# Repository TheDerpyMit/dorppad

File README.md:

# dorppad
heya! this is DorpPad, (or NikoKaltryxPad). It is a 6 button macropad with a rotate encoder meant for games or productivity!

# Features!!
- 6 customizable buttons for max productivity!
- a *beautiful* rotary encoder for volume control or whatever you wish :D
- pretty bulky (i will probably redesign this baha) case with 2 led's

i also wanted to leave a hole for the led's to shine through but i decided i can probably cut out the case and put thin blured out plastic to make it look like pixels but i wasn't so sure about it so i didn't do it in this version..

the code is very incomplete and mostly chatgpt since i plan on redoing it when i get the parts to make this 🥹

# Assembly

# PCB

# Schmatic

# Case parts!!

Back case to hold the PCB

Front cover so it looks beautiful!

And finally the whole case put together! (insert drumroll sound!!)

# BOM
| Item | Quantity | Price (USD) |
|-----|----------|-------------|
| Cherry MX Low Profile Switches | 6x | 1.26 |
| Blank DSA Keycaps | 6x | 1.50 |
| Xiao RP2040 | 1x | 6.75 |
| EC11B5AI Rotary Encoder | 1x | 0.61 |
| PCB | 1x | 9.82 |
| **Total (Approx.)** |  | **18-20 USD** |

# thank you so much for viewing this btw this was a very fun project to do! 💖

update: i will probably update this design so its more visually appealing since there's a lot of things i wanna fix

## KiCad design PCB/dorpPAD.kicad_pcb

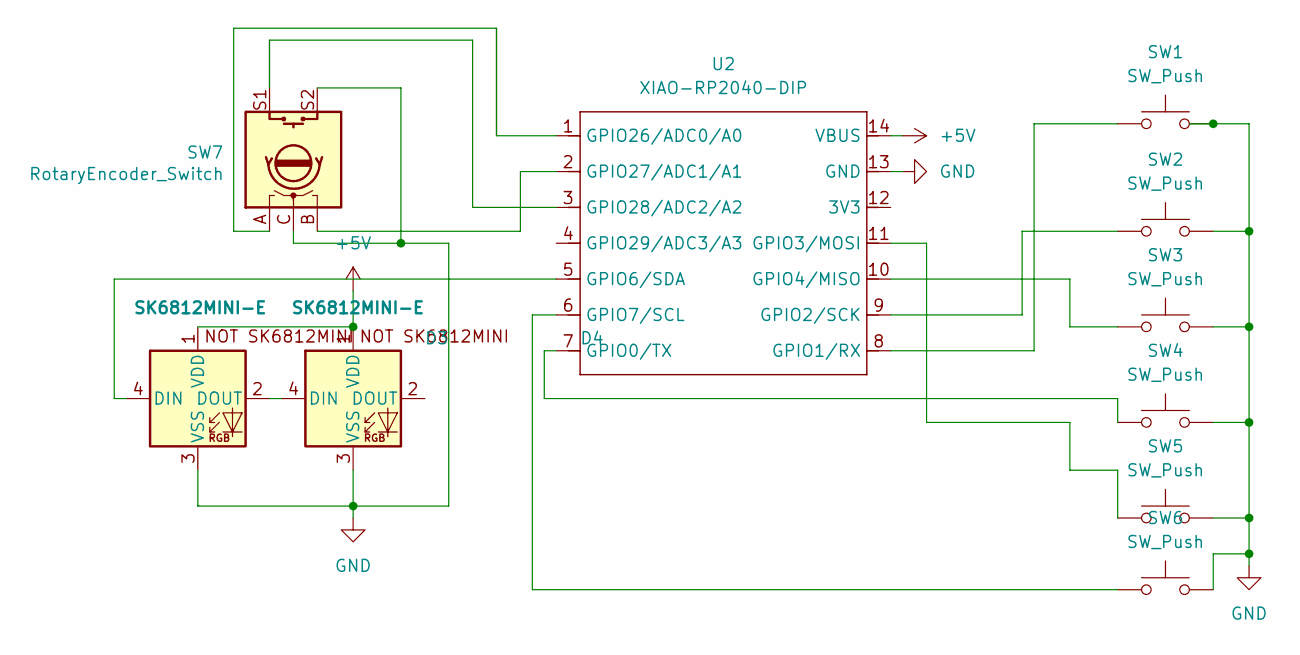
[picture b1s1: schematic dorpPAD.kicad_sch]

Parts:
D3, D4: SK6812MINI-E; MX_SK6812MINI-E_REV
SW1, SW2, SW3, SW4, SW5, SW6: SW_Push; SW_Cherry_MX_1.00u_PCB
SW7: RotaryEncoder_Switch; RotaryEncoder_Alps_EC11E-Switch_Vertical_H20mm
U2: XIAO-RP2040-DIP

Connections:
+5V: D3.1 (VDD), D4.1 (VDD), U2.14 (VBUS)
GND: D3.3 (VSS), D4.3 (VSS), SW1.2, SW2.2, SW3.2, SW4.2, SW5.2, SW6.2, SW7.C, SW7.S2, U2.13 (GND)
unnamed: D3.4 (DIN), U2.5 (GPIO6/SDA)
unnamed: D3.2 (DOUT), D4.4 (DIN)
unnamed: SW4.1, U2.7 (GPIO0/TX)
unnamed: SW1.1, U2.8 (GPIO1/RX)
unnamed: SW2.1, U2.9 (GPIO2/SCK)
unnamed: SW5.1, U2.11 (GPIO3/MOSI)
unnamed: SW3.1, U2.10 (GPIO4/MISO)
unnamed: SW6.1, U2.6 (GPIO7/SCL)
unnamed: SW7.A, U2.1 (GPIO26/ADC0/A0)
unnamed: SW7.B, U2.2 (GPIO27/ADC1/A1)
unnamed: SW7.S1, U2.3 (GPIO28/ADC2/A2)

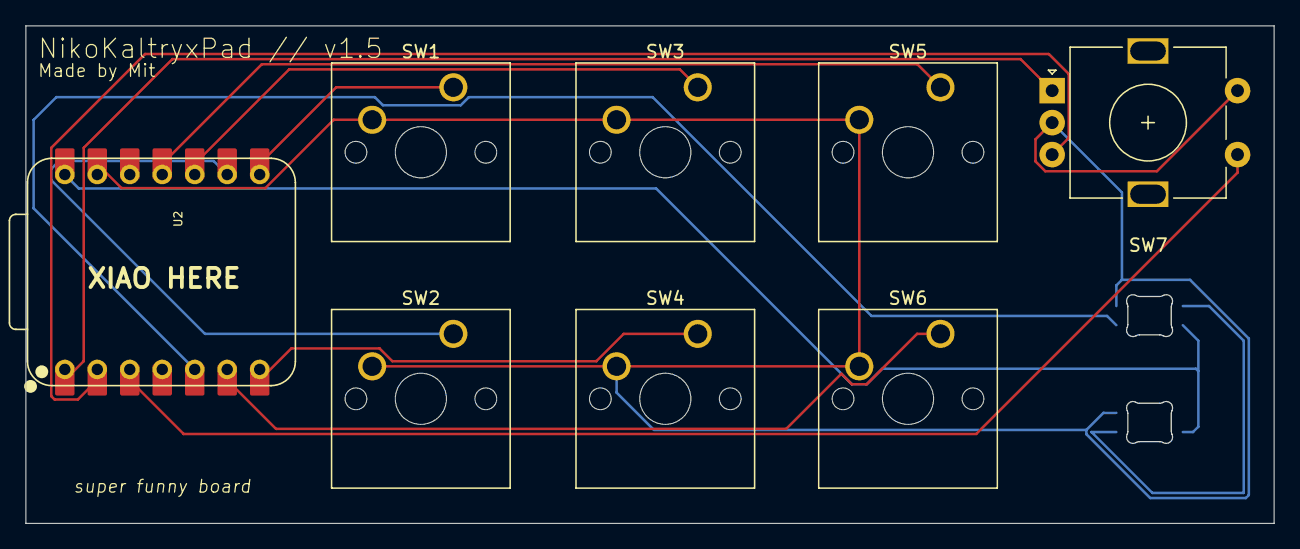
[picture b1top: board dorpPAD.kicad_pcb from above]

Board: 2 copper layers, 97.6 x 38.9 mm, 10 parts (0 on the bottom side), 13 nets.

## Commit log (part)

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2026-02-03 Revise README.md for DorpPad project details
    Updated README.md to provide detailed information about DorpPad, including features, assembly instructions, PCB images, schematic, case parts, and BOM.
2026-02-03 Rename finisheddesign.step to case.step
2026-02-04 Update README with additional images for PCB and Schmatic
    Added new images for PCB and Schmatic sections in README.
